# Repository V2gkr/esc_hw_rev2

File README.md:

# ESC HW Rev2 - E-Bike BLDC Motor Driver

Rev2 hardware for an electronic speed controller (ESC) for an e-bike. Designed in KiCad.

## Key Specifications

| Parameter | Value |
|---|---|
| Nominal battery voltage | 36 V |
| Nominal motor power | 250 W |
| MCU | STM32G431CBT6 |
| Gate driver | DRV8320S |
| Phase current sensing |  low-side shunts |
| Rotor position feedback | Hall sensors |
| Interfaces | CAN FD, UART |
| Indication | LEDs (Green / Red) |
| Control | Reset button |

## Board Architecture

The project is split into several KiCad hierarchical schematic sheets:

- **MCU.kicad_sch** - STM32G431CBT6 support circuitry: power supply, crystals, debug interface, reset button, LEDs.
- **Power.kicad_sch** - 36 V input power stage, protection, DC/DC converters for logic and gate driver supply.
- **Inverter.kicad_sch** - three-phase power inverter stage based on DRV8320S and power MOSFETs.
- **Measurements.kicad_sch** - phase current sensing circuitry (3 low-side shunts) and Hall sensor interfaces.
- **CAN.kicad_sch** - CAN FD transceiver and supporting circuitry.
- **BLDC_Test.kicad_sch / BLDC_Test.kicad_pcb / BLDC_Test.kicad_pro** - top-level schematic and PCB layout tying all sheets above together.

## Key Subsystems

### Power Stage
Three-phase MOSFET inverter driven by the **DRV8320S** gate driver (built-in protection: overtemperature, overcurrent, gate drive undervoltage, etc.).

### Current and Rotor Position Sensing
- 3 low-side shunts - phase current measurement for FOC/trapezoidal commutation and overcurrent protection.
- Hall sensors - rotor position detection for low-speed commutation and start-up under load.

### Communication Interfaces
- **CAN FD** - primary control/telemetry channel (e.g. integration with a BMS or a central e-bike controller).
- **UART** - debugging, logging, alternative control/flashing channel.

### Indication and Control
- Green / Red LEDs - status indication (ready, fault, CAN activity, etc. â€” defined by firmware).
- Reset button - hardware MCU reset.

## Project Status

Hardware only (rev2). Firmware is maintained in a separate repository (see [`esc_fw_rev2`](https://github.com/V2gkr/esc_fw_rev2/tree/main)).

## TODO
- [ ] Export schematics to PDF for quick viewing without KiCad
- [ ] Bill of Materials (BOM)
- [ ] Board photos/renders
- [ ] Datasheet links for key components (DRV8320S, STM32G431CBT6)

## Tools
Designed in **KiCad**.

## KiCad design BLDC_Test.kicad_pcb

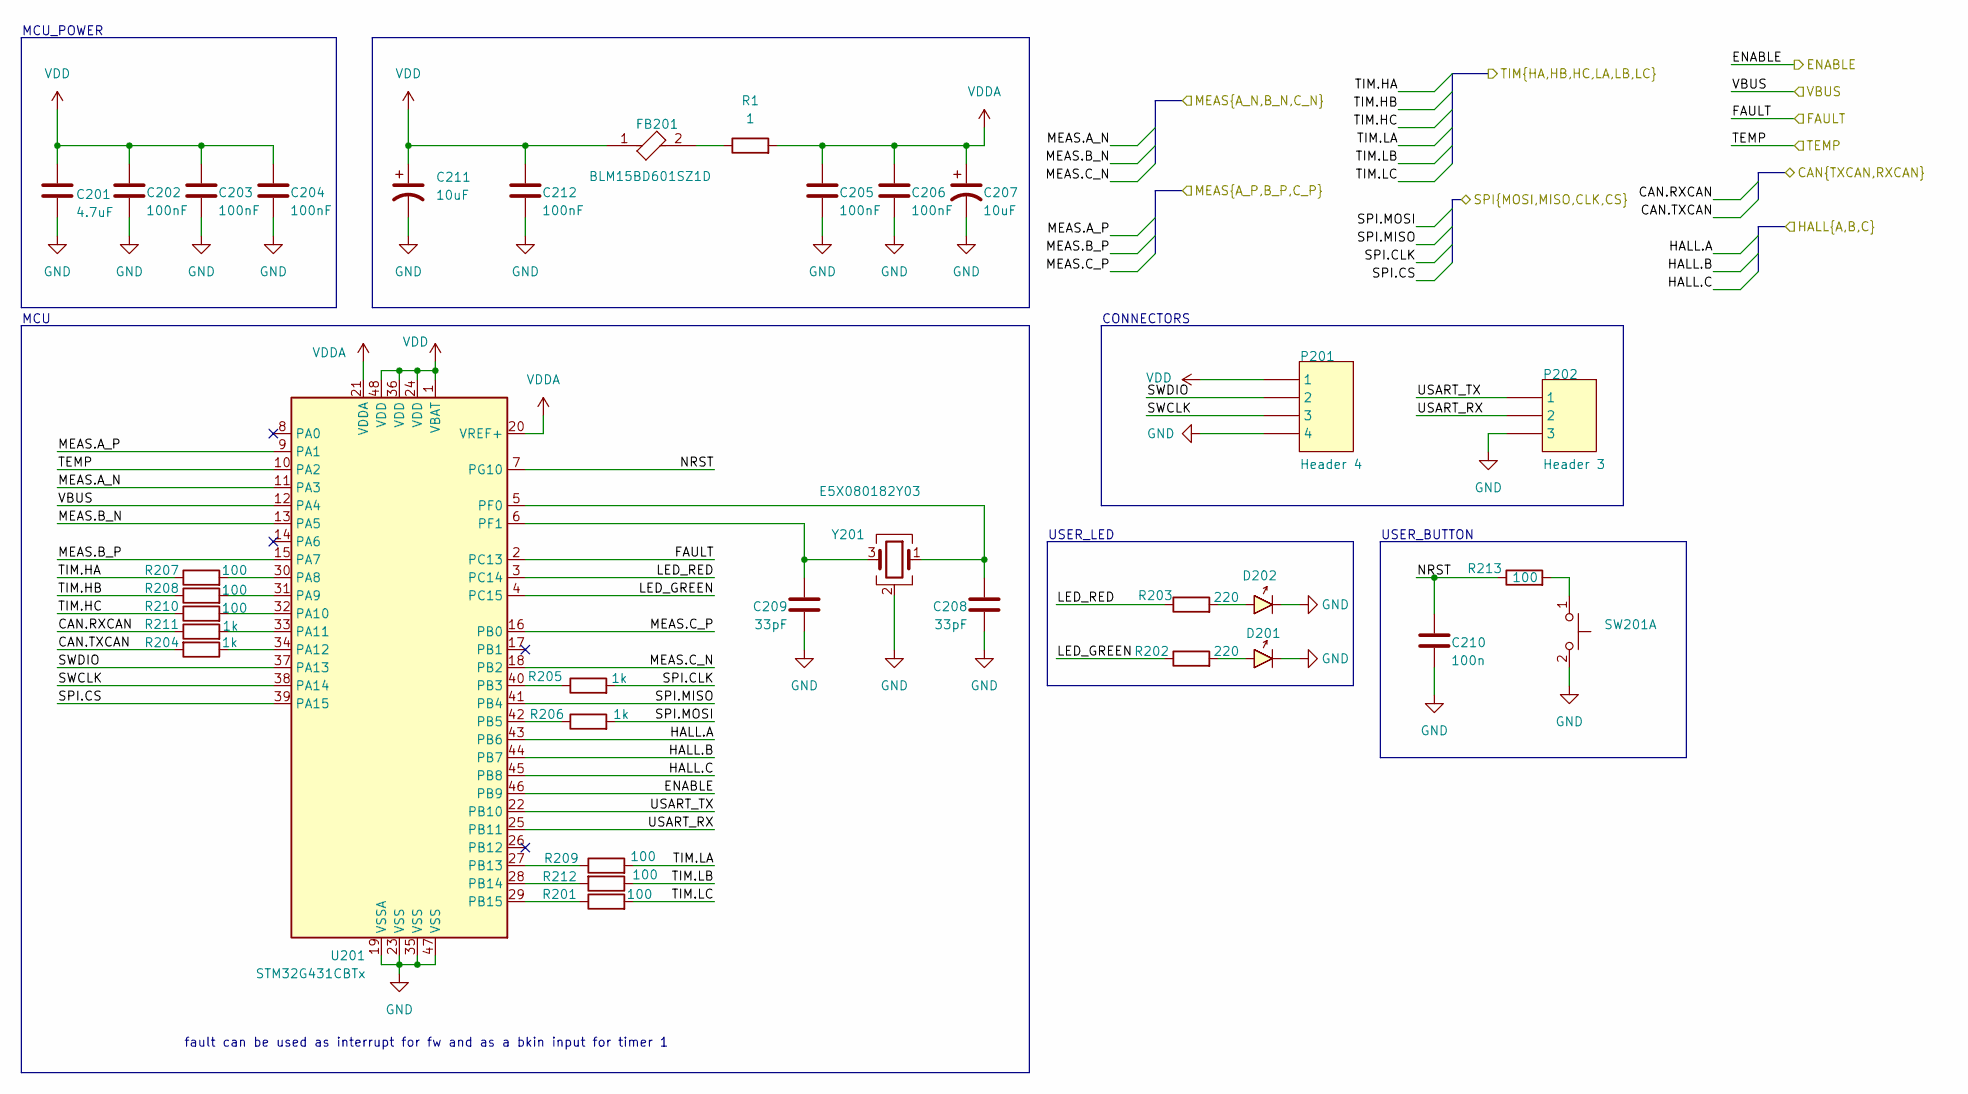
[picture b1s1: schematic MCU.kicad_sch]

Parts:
C201: 4.7uF; C_0603_1608Metric_Pad1.08x0.95mm_HandSolder
C202, C203, C204, C205, C206, C212: 100nF; C_0603_1608Metric_Pad1.08x0.95mm_HandSolder
C207, C211: 10uF; CP_EIA-2012-15_AVX-P_HandSolder
C208, C209: 33pF; C_0603_1608Metric_Pad1.08x0.95mm_HandSolder
C210: 100n; C_0603_1608Metric_Pad1.08x0.95mm_HandSolder
D201, D202: Common diode; LED_0603_1608Metric_Pad1.05x0.95mm_HandSolder; REVERSE VOLTAGE 1000V; MANUFACTURER PART NUMBER US1M-E3/61T; DIGIKEY DESCRIPTION DIODE GEN PURP 1KV 1A DO214AC
FB201: BLM15BD601SZ1D; L_0603_1608Metric_Pad1.05x0.95mm_HandSolder
P201: Header 4; PinHeader_1x04_P2.54mm_Vertical
P202: Header 3; PinHeader_1x03_P2.54mm_Vertical
R1: 1; R_0603_1608Metric_Pad0.98x0.95mm_HandSolder
R201, R207, R208, R209, R210, R212, R213: 100; R_0603_1608Metric_Pad0.98x0.95mm_HandSolder
R202, R203: 220; R_0603_1608Metric_Pad0.98x0.95mm_HandSolder
R204, R205, R206, R211: 1k; R_0603_1608Metric_Pad0.98x0.95mm_HandSolder
SW201: PTS647SM38SMTR2LFS; SW_SPST_TL3305A; RATINGS IP40
U201: STM32G431CBTx; LQFP-48_7x7mm_P0.5mm
Y201: E5X080182Y03; Crystal_SMD_WE_CFPX-104-4Pin_5.0x3.2mm; FREQUENCY TOLERANCE 0.07%

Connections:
/can/CAN.RXCAN: R211.1; also elsewhere on the board
/can/CAN.TXCAN: R204.2; also elsewhere on the board
/inverter/ENABLE: U201.46 (PB9); also elsewhere on the board
/inverter/FAULT: U201.2 (PC13); also elsewhere on the board
/inverter/MEAS.A_N: U201.11 (PA3); also elsewhere on the board
/inverter/MEAS.B_N: U201.13 (PA5); also elsewhere on the board
/inverter/MEAS.C_N: U201.18 (PB2); also elsewhere on the board
/inverter/SPI.CLK: R205.2; also elsewhere on the board
/inverter/SPI.CS: U201.39 (PA15); also elsewhere on the board
/inverter/SPI.MISO: U201.41 (PB4); also elsewhere on the board
/inverter/SPI.MOSI: R206.2; also elsewhere on the board
/inverter/TIM.HA: R207.1; also elsewhere on the board
/inverter/TIM.HB: R208.1; also elsewhere on the board
/inverter/TIM.HC: R210.1; also elsewhere on the board
/inverter/TIM.LA: R209.2; also elsewhere on the board
/inverter/TIM.LB: R212.1; also elsewhere on the board
/inverter/TIM.LC: R201.2; also elsewhere on the board
/mcu/HALL.A: U201.43 (PB6); also elsewhere on the board
/mcu/HALL.B: U201.44 (PB7); also elsewhere on the board
/mcu/HALL.C: U201.45 (PB8); also elsewhere on the board
/mcu/LED_GREEN: R202.1, U201.4 (PC15)
/mcu/LED_RED: R203.1, U201.3 (PC14)
/mcu/MEAS.A_P: U201.9 (PA1); also elsewhere on the board
/mcu/MEAS.B_P: U201.15 (PA7); also elsewhere on the board
/mcu/MEAS.C_P: U201.16 (PB0); also elsewhere on the board
/mcu/NRST: C210.1, R213.1, U201.7 (PG10)
/mcu/SWCLK: P201.3, U201.38 (PA14)
/mcu/SWDIO: P201.2, U201.37 (PA13)
/mcu/TEMP: U201.10 (PA2); also elsewhere on the board
/mcu/USART_RX: P202.2, U201.25 (PB11)
/mcu/USART_TX: P202.1, U201.22 (PB10)
/mcu/VBUS: U201.12 (PA4); also elsewhere on the board
GND: C201.2, C202.2, C203.2, C204.2, C205.2, C206.2, C207.2, C208.2, C209.2, C210.2, C211.2, C212.2, D201.1 (C), D202.1 (C), P201.4, P202.3, SW201.2 (D), U201.19 (VSSA), U201.23 (VSS), U201.35 (VSS), U201.47 (VSS), Y201.2 (G), Y201.4 (G); also elsewhere on the board
unnamed: D201.2 (A), R202.2
unnamed: D202.2 (A), R203.2
unnamed: FB201.2, R1.1
unnamed: R213.2, SW201.1 (C)
unnamed: R207.2, U201.30 (PA8)
unnamed: R208.2, U201.31 (PA9)
unnamed: R210.2, U201.32 (PA10)
unnamed: R211.2, U201.33 (PA11)
unnamed: R204.1, U201.34 (PA12)
unnamed: R205.1, U201.40 (PB3)
unnamed: R206.1, U201.42 (PB5)
unnamed: R209.1, U201.27 (PB13)
unnamed: R212.2, U201.28 (PB14)
unnamed: R201.1, U201.29 (PB15)
unnamed: C208.1, U201.5 (PF0), Y201.1
unnamed: C209.1, U201.6 (PF1), Y201.3
VDD: C201.1, C202.1, C203.1, C204.1, C211.1, C212.1, FB201.1, P201.1, U201.1 (VBAT), U201.24 (VDD), U201.36 (VDD), U201.48 (VDD); also elsewhere on the board
VDDA: C205.1, C206.1, C207.1, R1.2, U201.20 (VREF+), U201.21 (VDDA); also elsewhere on the board

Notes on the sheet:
USER_LED
MCU_POWER
CONNECTORS
USER_BUTTON
MCU
fault can be used as interrupt for fw and as a bkin input for timer 1

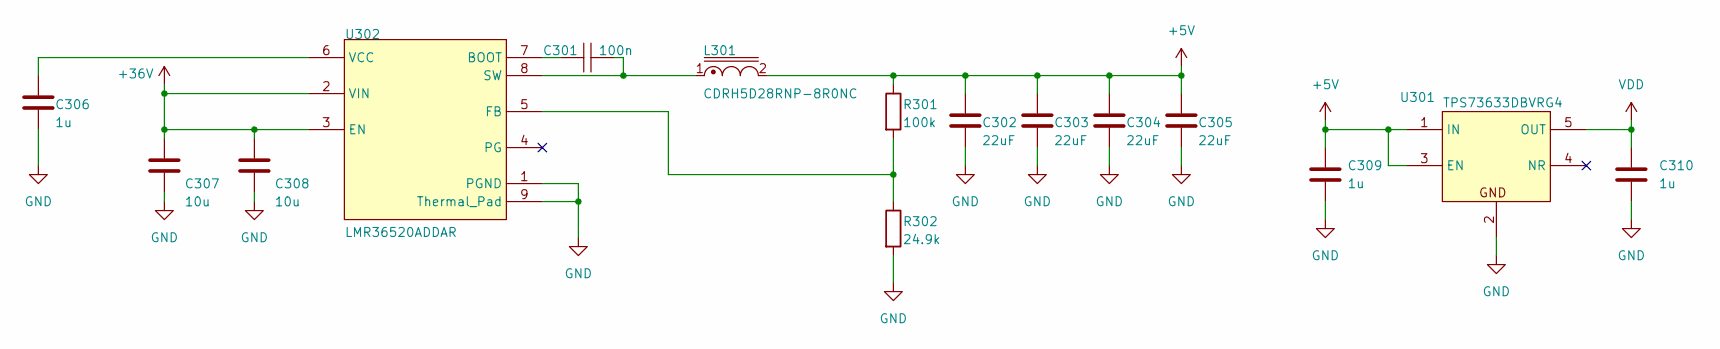
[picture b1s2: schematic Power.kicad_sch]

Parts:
C301: 100n; C_0603_1608Metric_Pad1.08x0.95mm_HandSolder
C302, C303, C304, C305: 22uF; C_0805_2012Metric_Pad1.18x1.45mm_HandSolder
C306, C309, C310: 1u; C_0603_1608Metric_Pad1.08x0.95mm_HandSolder
C307, C308: 10u; C_0805_2012Metric_Pad1.18x1.45mm_HandSolder
L301: CDRH5D28RNP-8R0NC; MANUFACTURER PART NUMBER PA4320.153NLT
R301: 100k; R_0603_1608Metric_Pad0.98x0.95mm_HandSolder
R302: 24.9k; R_0603_1608Metric_Pad0.98x0.95mm_HandSolder
U301: TPS73633DBVRG4; SOT-23-5_HandSoldering; RATING Catalog; PARTNUMBER TPS73633DBVRG4
U302: LMR36520ADDAR; FP-DDA0008J-IPC_B

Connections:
+5V: C302.1, C303.1, C304.1, C305.1, C309.1, L301.2, R301.1, U301.1 (IN), U301.3 (EN); also elsewhere on the board
+36V: C307.1, C308.1, U302.2 (VIN), U302.3 (EN); also elsewhere on the board
GND: C302.2, C303.2, C304.2, C305.2, C306.2, C307.2, C308.2, C309.2, C310.2, R302.2, U301.2 (GND), U302.1 (PGND), U302.9 (Thermal_Pad); also elsewhere on the board
unnamed: C301.2, U302.7 (BOOT)
unnamed: R301.2, R302.1, U302.5 (FB)
unnamed: C301.1, L301.1, U302.8 (SW)
unnamed: C306.1, U302.6 (VCC)
VDD: C310.1, U301.5 (OUT); also elsewhere on the board

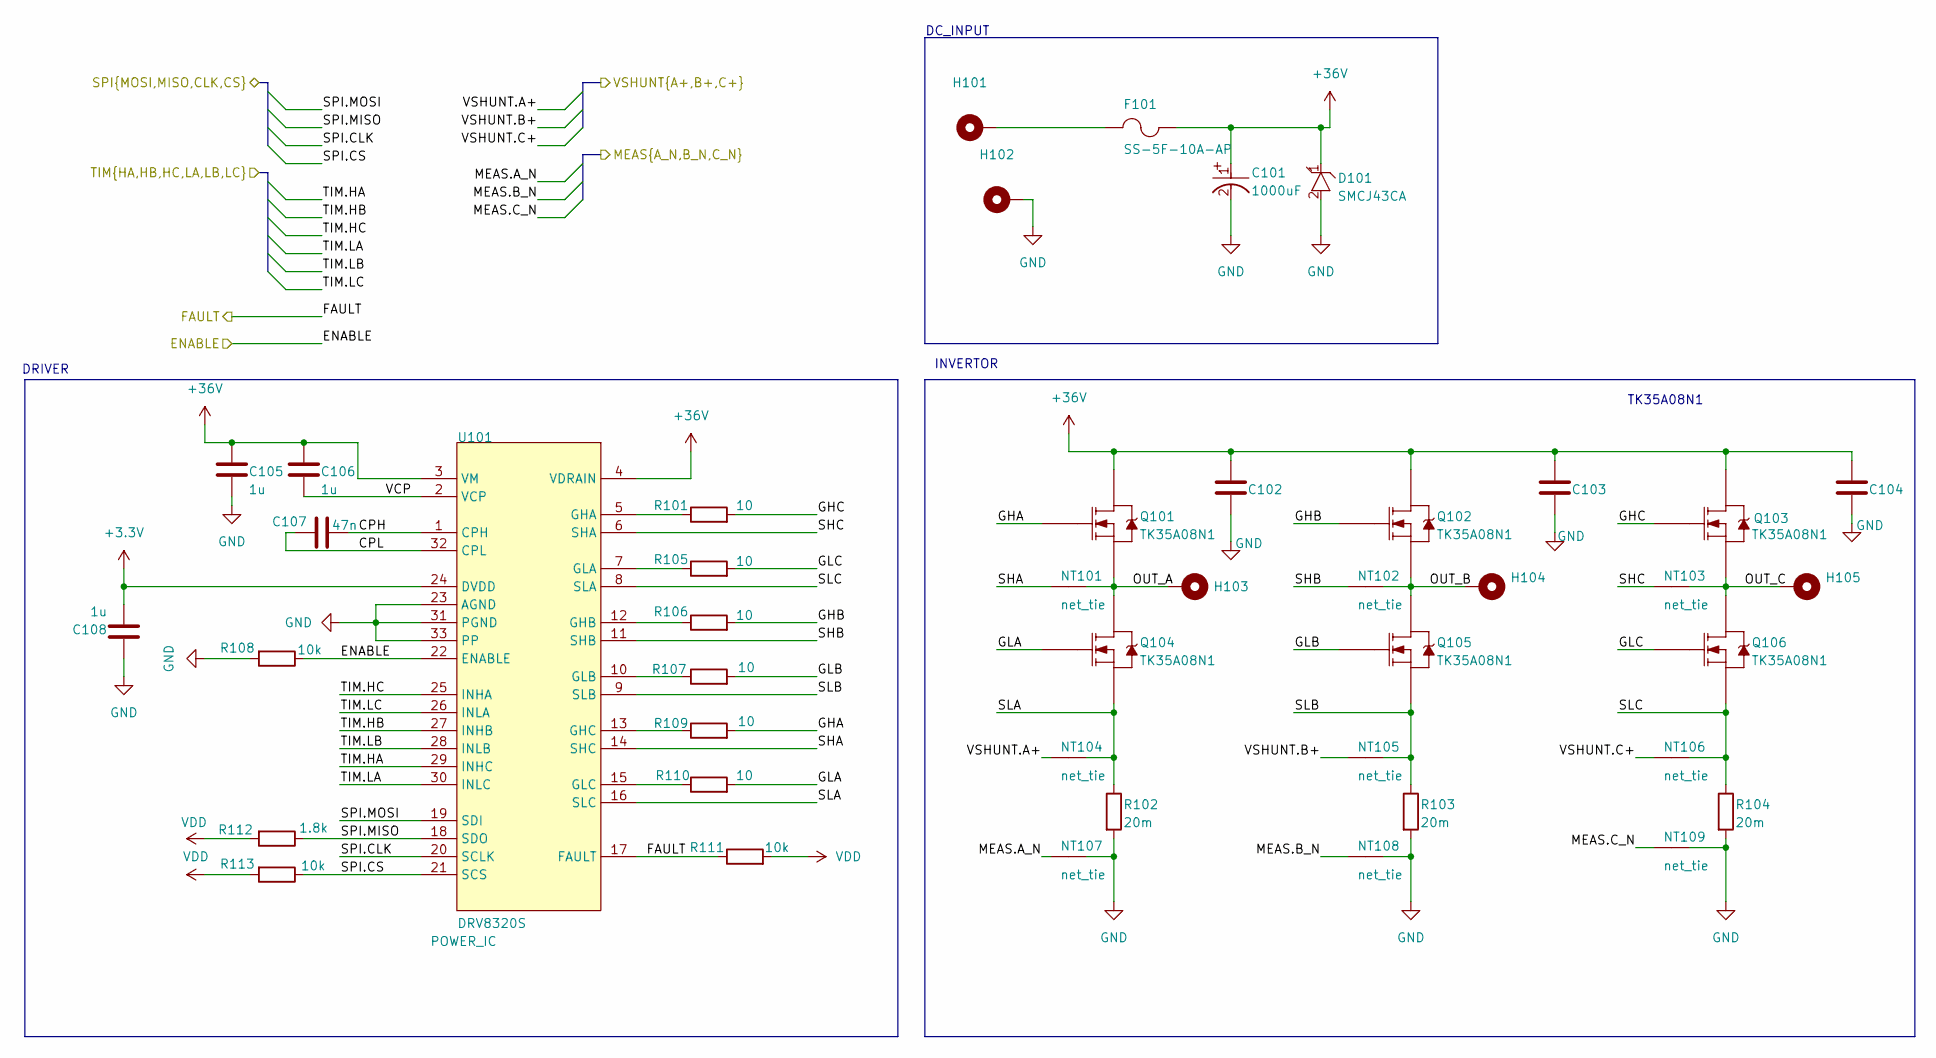
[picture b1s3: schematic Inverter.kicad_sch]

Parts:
C101: 1000uF; PCAP_7_5mm; VOLTAGE RATING (DC) 50V; TOLERANCE 20%; MANUFACTURER PART NUMBER EEUFM1H471
C102, C103, C104: 1812B105K101CT; C_1812_4532Metric_Pad1.57x3.40mm_HandSolder
C105: 1u; C_1210_3225Metric_Pad1.33x2.70mm_HandSolder
C106, C108: 1u; C_0603_1608Metric_Pad1.08x0.95mm_HandSolder
C107: 47n; C_0603_1608Metric_Pad1.08x0.95mm_HandSolder
D101: SMCJ43CA; D_SMC; REVERSE VOLTAGE 1000V; MANUFACTURER PART NUMBER US1M-E3/61T; DIGIKEY DESCRIPTION DIODE GEN PURP 1KV 1A DO214AC
F101: SS-5F-10A-AP; FUSE_SS-5F_COB; MANUFACTURER_PART_NUMBER SS-5F-1.25A-AP
H101, H102, H103, H104, H105: phase connector; phase_cable_soldering_hole
NT101, NT102, NT103: net_tie; NetTie-2_SMD_Pad0.5mm
NT104, NT105, NT106, NT107, NT108, NT109: net_tie; NetTie-2_SMD_Pad0.3mm
Q101, Q102, Q103, Q104, Q105, Q106: TK35A08N1; TO-220-3_Vertical
R101, R105, R106, R107, R109, R110: 10; R_0603_1608Metric_Pad0.98x0.95mm_HandSolder
R102, R103, R104: 20m; R_2512_6332Metric_Pad1.40x3.35mm_HandSolder
R108, R111, R113: 10k; R_0603_1608Metric_Pad0.98x0.95mm_HandSolder
R112: 1.8k; R_0603_1608Metric_Pad0.98x0.95mm_HandSolder
U101: DRV8320S; QFN50P500X500X80-33N

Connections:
+3.3V: C108.2, U101.24 (DVDD)
+36V: C101.1 (A), C102.1, C103.1, C104.1, C105.1, C106.1, D101.1 (C), F101.2, Q101.2 (D), Q102.2 (D), Q103.2 (D), U101.3 (VM), U101.4 (VDRAIN); also elsewhere on the board
/inverter/CPH: C107.2, U101.1 (CPH)
/inverter/CPL: C107.1, U101.32 (CPL)
/inverter/ENABLE: R108.1, U101.22 (ENABLE); also elsewhere on the board
/inverter/FAULT: R111.1, U101.17 (FAULT); also elsewhere on the board
/inverter/GHA: Q101.1 (G), R109.2
/inverter/GHB: Q102.1 (G), R106.2
/inverter/GHC: Q103.1 (G), R101.2
/inverter/GLA: Q104.1 (G), R110.2
/inverter/GLB: Q105.1 (G), R107.2
/inverter/GLC: Q106.1 (G), R105.2
/inverter/MEAS.A_N: NT107.2; also elsewhere on the board
/inverter/MEAS.B_N: NT108.2; also elsewhere on the board
/inverter/MEAS.C_N: NT109.2; also elsewhere on the board
/inverter/OUT_A: H103.1 (1_1), NT101.1, Q101.3 (S), Q104.2 (D)
/inverter/OUT_B: H104.1 (1_1), NT102.1, Q102.3 (S), Q105.2 (D)
/inverter/OUT_C: H105.1 (1_1), NT103.1, Q103.3 (S), Q106.2 (D)
/inverter/SHA: NT101.2, U101.14 (SHC)
/inverter/SHB: NT102.2, U101.11 (SHB)
/inverter/SHC: NT103.2, U101.6 (SHA)
/inverter/SLA: NT104.1, Q104.3 (S), R102.1, U101.16 (SLC)
/inverter/SLB: NT105.1, Q105.3 (S), R103.1, U101.9 (SLB)
/inverter/SLC: NT106.1, Q106.3 (S), R104.1, U101.8 (SLA)
/inverter/SPI.CLK: U101.20 (SCLK); also elsewhere on the board
/inverter/SPI.CS: R113.1, U101.21 (SCS); also elsewhere on the board
/inverter/SPI.MISO: R112.1, U101.18 (SDO); also elsewhere on the board
/inverter/SPI.MOSI: U101.19 (SDI); also elsewhere on the board
/inverter/TIM.HA: U101.29 (INHC); also elsewhere on the board
/inverter/TIM.HB: U101.27 (INHB); also elsewhere on the board
/inverter/TIM.HC: U101.25 (INHA); also elsewhere on the board
/inverter/TIM.LA: U101.30 (INLC); also elsewhere on the board
/inverter/TIM.LB: U101.28 (INLB); also elsewhere on the board
/inverter/TIM.LC: U101.26 (INLA); also elsewhere on the board
/inverter/VCP: C106.2, U101.2 (VCP)
/inverter/VSHUNT.A+: NT104.2; also elsewhere on the board
/inverter/VSHUNT.B+: NT105.2; also elsewhere on the board
/inverter/VSHUNT.C+: NT106.2; also elsewhere on the board
GND: C101.2 (B), C102.2, C103.2, C104.2, C105.2, C108.1, D101.2 (A), H102.1 (1_1), NT107.1, NT108.1, NT109.1, R102.2, R103.2, R104.2, R108.2, U101.23 (AGND), U101.31 (PGND), U101.33 (PP); also elsewhere on the board
unnamed: F101.1, H101.1 (1_1)
unnamed: R101.1, U101.5 (GHA)
unnamed: R106.1, U101.12 (GHB)
unnamed: R109.1, U101.13 (GHC)
unnamed: R105.1, U101.7 (GLA)
unnamed: R107.1, U101.10 (GLB)
unnamed: R110.1, U101.15 (GLC)
VDD: R111.2, R112.2, R113.2; also elsewhere on the board

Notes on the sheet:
TK35A08N1
INVERTOR
DRIVER
DC_INPUT

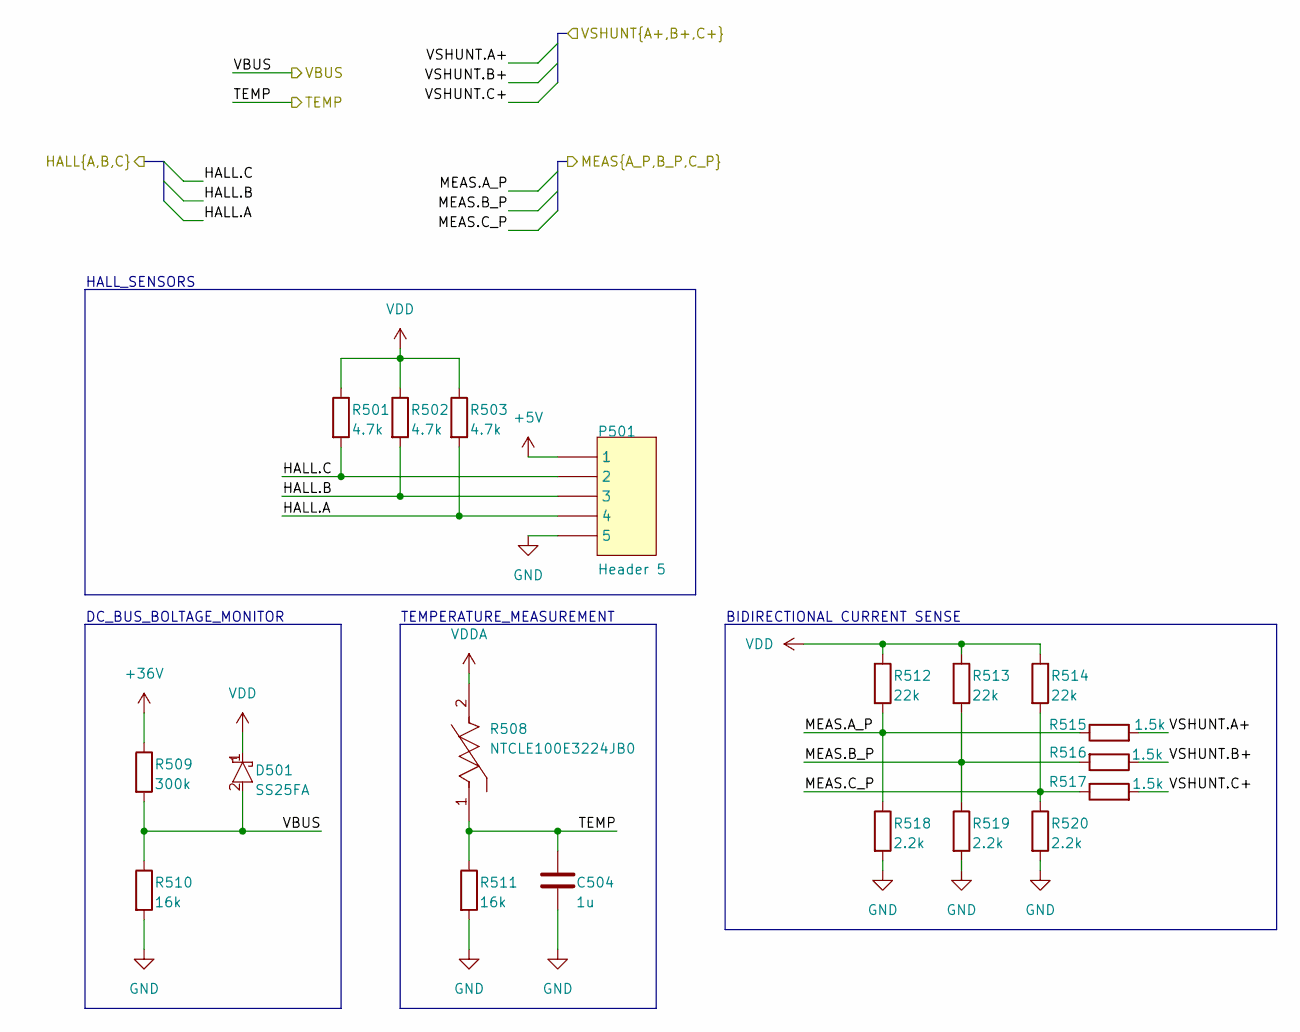
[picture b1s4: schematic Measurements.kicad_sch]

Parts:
C504: 1u; C_0603_1608Metric_Pad1.08x0.95mm_HandSolder
D501: SS25FA; D_SOD-323; REVERSE VOLTAGE 1000V; MANUFACTURER PART NUMBER US1M-E3/61T; DIGIKEY DESCRIPTION DIODE GEN PURP 1KV 1A DO214AC
P501: Header 5; PinHeader_1x05_P2.54mm_Vertical
R501, R502, R503: 4.7k; R_0603_1608Metric_Pad0.98x0.95mm_HandSolder
R508: NTCLE100E3224JB0; FP-NTCLE100E3224JB0-MFG; TOLERANCE 5%; RESISTANCE TOLERANCE 5%
R509: 300k; R_0603_1608Metric_Pad0.98x0.95mm_HandSolder
R510, R511: 16k; R_0603_1608Metric_Pad0.98x0.95mm_HandSolder
R512, R513, R514: 22k; R_0603_1608Metric_Pad0.98x0.95mm_HandSolder
R515, R516, R517: 1.5k; R_0603_1608Metric_Pad0.98x0.95mm_HandSolder
R518, R519, R520: 2.2k; R_0603_1608Metric_Pad0.98x0.95mm_HandSolder

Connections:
+5V: P501.1; also elsewhere on the board
+36V: R509.1; also elsewhere on the board
/inverter/VSHUNT.A+: R515.2; also elsewhere on the board
/inverter/VSHUNT.B+: R516.1; also elsewhere on the board
/inverter/VSHUNT.C+: R517.2; also elsewhere on the board
/mcu/HALL.A: P501.4, R503.2; also elsewhere on the board
/mcu/HALL.B: P501.3, R502.2; also elsewhere on the board
/mcu/HALL.C: P501.2, R501.2; also elsewhere on the board
/mcu/MEAS.A_P: R512.2, R515.1, R518.1; also elsewhere on the board
/mcu/MEAS.B_P: R513.2, R516.2, R519.1; also elsewhere on the board
/mcu/MEAS.C_P: R514.2, R517.1, R520.1; also elsewhere on the board
/mcu/TEMP: C504.1, R508.1, R511.1; also elsewhere on the board
/mcu/VBUS: D501.2 (A), R509.2, R510.1; also elsewhere on the board
GND: C504.2, P501.5, R510.2, R511.2, R518.2, R519.2, R520.2; also elsewhere on the board
VDD: D501.1 (C), R501.1, R502.1, R503.1, R512.1, R513.1, R514.1; also elsewhere on the board
VDDA: R508.2; also elsewhere on the board

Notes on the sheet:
HALL_SENSORS
DC_BUS_BOLTAGE_MONITOR
BIDIRECTIONAL CURRENT SENSE
TEMPERATURE_MEASUREMENT

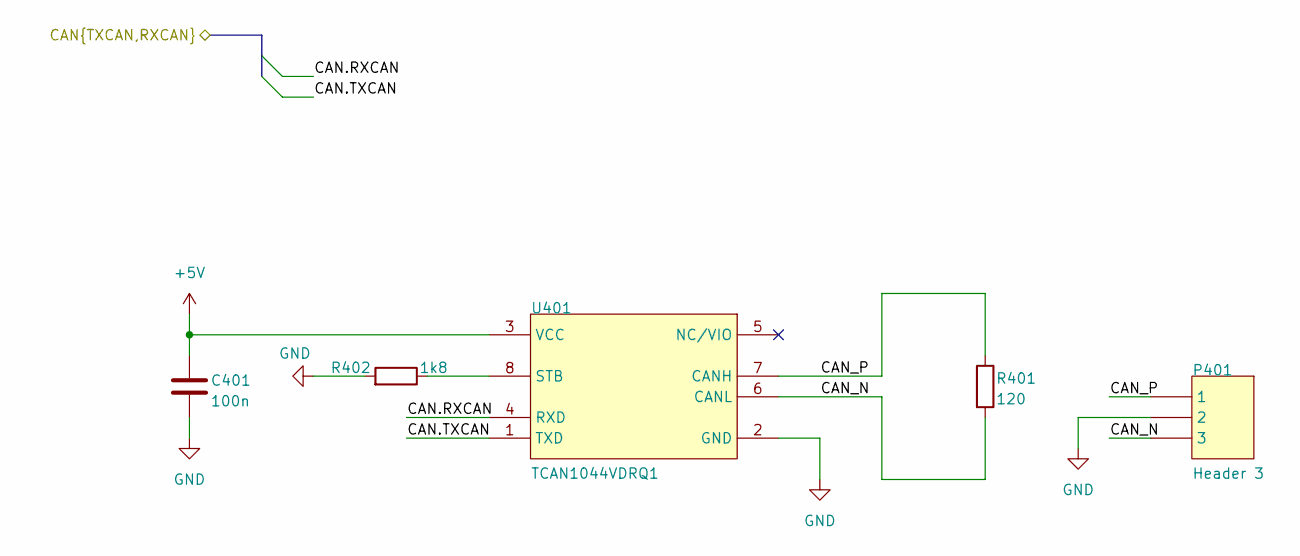
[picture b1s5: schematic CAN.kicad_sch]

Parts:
C401: 100n; C_0603_1608Metric_Pad1.08x0.95mm_HandSolder
P401: Header 3; PinHeader_1x03_P2.54mm_Vertical
R401: 120; R_0603_1608Metric_Pad0.98x0.95mm_HandSolder
R402: 1k8; R_0603_1608Metric_Pad0.98x0.95mm_HandSolder
U401: TCAN1044VDRQ1; SO-8_3.9x4.9mm_P1.27mm

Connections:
+5V: C401.1, U401.3 (VCC); also elsewhere on the board
/can/CAN.RXCAN: U401.4 (RXD); also elsewhere on the board
/can/CAN.TXCAN: U401.1 (TXD); also elsewhere on the board
/can/CAN_N: P401.3, R401.2, U401.6 (CANL)
/can/CAN_P: P401.1, R401.1, U401.7 (CANH)
GND: C401.2, P401.2, R402.2, U401.2 (GND); also elsewhere on the board
unnamed: R402.1, U401.8 (STB)

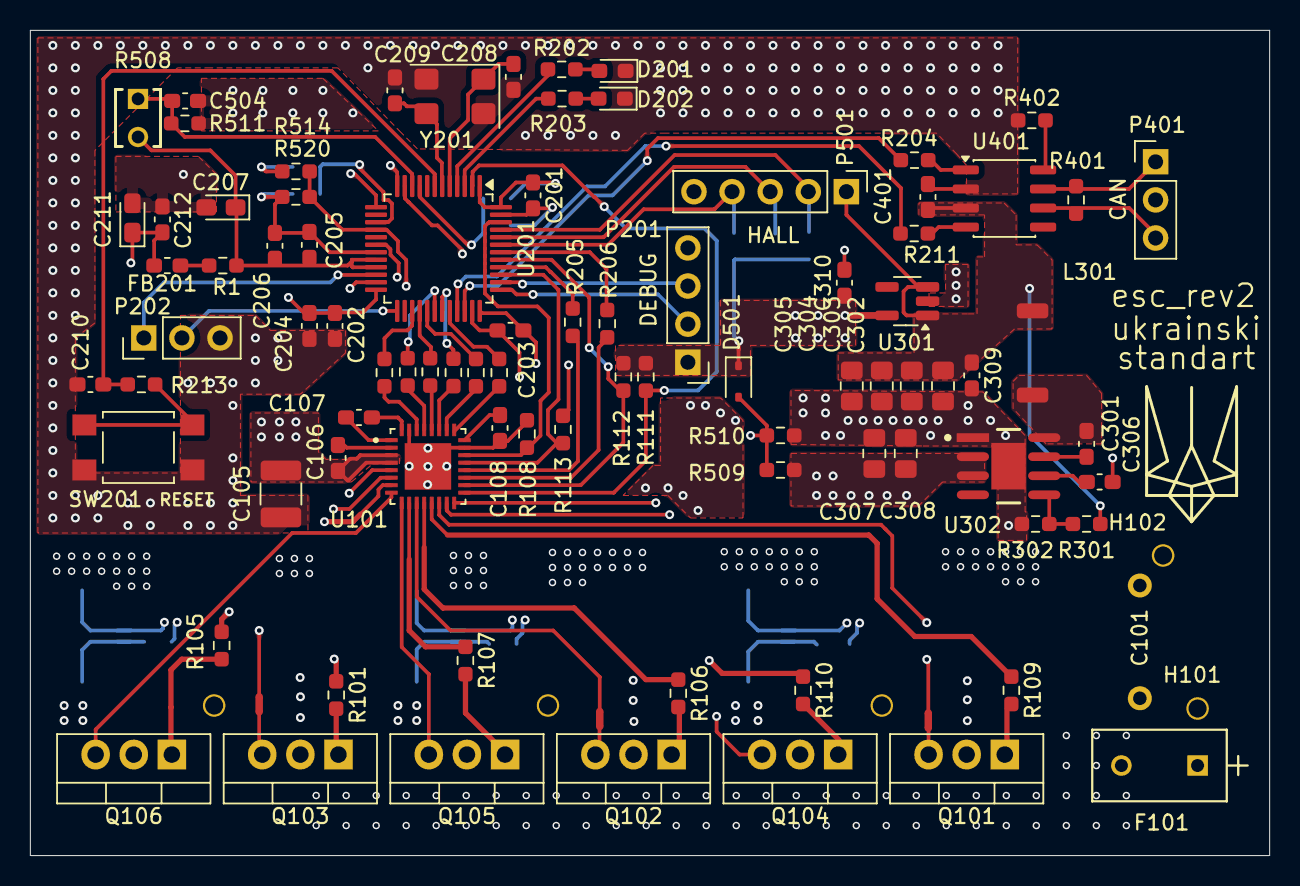
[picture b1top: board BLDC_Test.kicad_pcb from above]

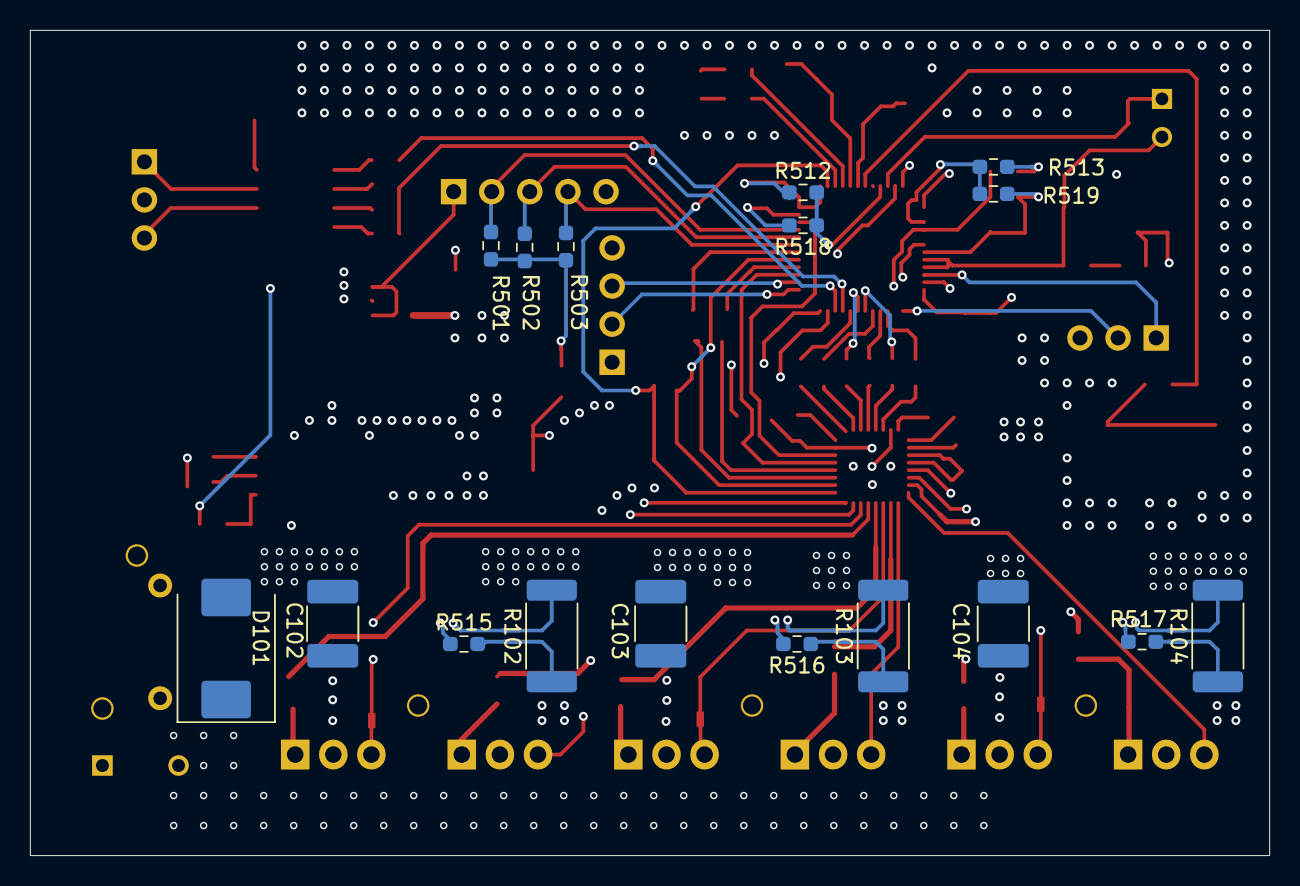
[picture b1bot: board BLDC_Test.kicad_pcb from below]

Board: 6 copper layers, 82.6 x 55.0 mm, 117 parts (23 on the bottom side), 89 nets.

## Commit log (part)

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2026-02-26 added names to sheets
2026-02-26 changed nets
2026-02-27 changed schematic and pcb to kicad style
2026-02-27 changed phases a and c
2026-03-01 routed power polygons
2026-03-05 completed routing
2026-03-06 fixed small errors in schematic
2026-03-09 fixed errors from review
2026-03-10 final changes and sending to production

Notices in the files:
parts and their libraries:
COPYRIGHT: Copyright (C) 2025 Ultra Librarian. All rights reserved.
